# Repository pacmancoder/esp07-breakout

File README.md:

# esp07-breakout
Crude ESP-07 module breakout board intended for toner transfer method DIY PCB production.

Use [Mirrored_Front_Layer.svg](Mirrored_Front_Layer.svg) file for printing with 100% scale;  No additional mirroring required.
Also 2 additional *almost* parallel jumper wires should be placed on the backside of the PCB.

|Render               |Photo              |
|---------------------|-------------------|
|||

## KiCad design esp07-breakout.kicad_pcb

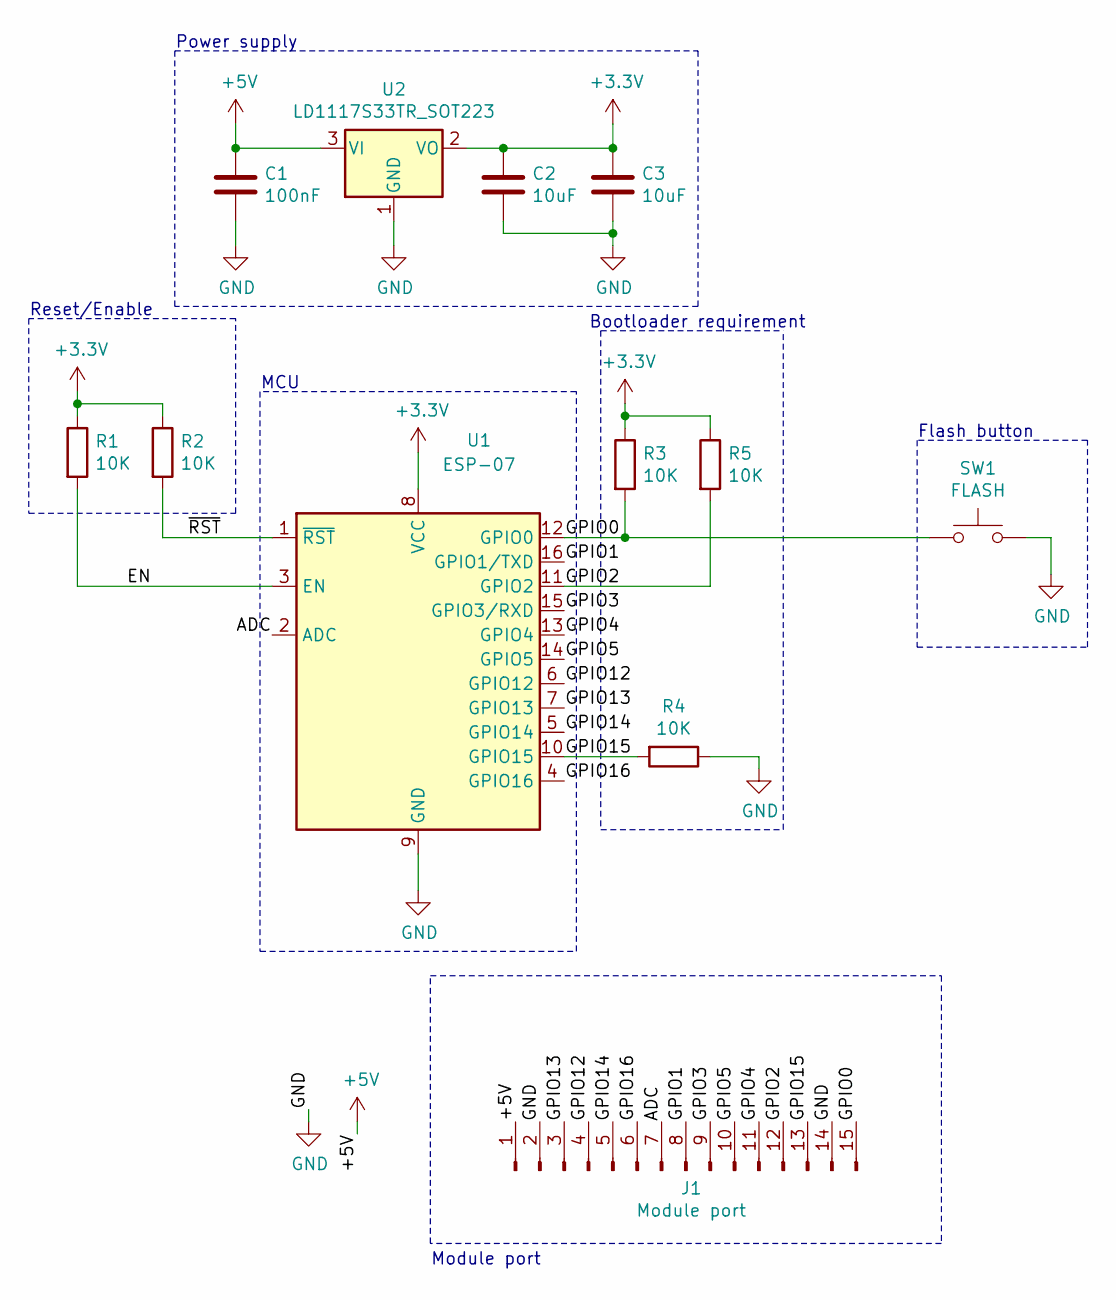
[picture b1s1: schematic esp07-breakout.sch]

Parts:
C1: 100nF; C_0805_2012Metric_Pad1.15x1.40mm_HandSolder
C2, C3: 10uF; C_0805_2012Metric_Pad1.15x1.40mm_HandSolder
J1: Module port; PinHeader_1x15_P2.54mm_Horizontal
R1, R2, R3, R4, R5: 10K; R_0805_2012Metric_Pad1.15x1.40mm_HandSolder
SW1: FLASH; SW_SPST_PTS645
U1: ESP-07
U2: LD1117S33TR_SOT223; SOT-223-3_TabPin2

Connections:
+3V3: C2.1, C3.1, R1.1, R2.1, R3.1, R5.1, U1.8 (VCC), U2.2 (VO)
+5V: C1.1, J1.1, U2.3 (VI)
/ADC: J1.7, U1.2 (ADC)
/EN: R1.2, U1.3 (EN)
/GPIO0: J1.15, R3.2, SW1.1, U1.12 (GPIO0)
/GPIO1: J1.8, U1.16 (GPIO1/TXD)
/GPIO2: J1.12, R5.2, U1.11 (GPIO2)
/GPIO3: J1.9, U1.15 (GPIO3/RXD)
/GPIO4: J1.11, U1.13 (GPIO4)
/GPIO5: J1.10, U1.14 (GPIO5)
/GPIO12: J1.4, U1.6 (GPIO12)
/GPIO13: J1.3, U1.7 (GPIO13)
/GPIO14: J1.5, U1.5 (GPIO14)
/GPIO15: J1.13, R4.2, U1.10 (GPIO15)
/GPIO16: J1.6, U1.4 (GPIO16)
/~RST: R2.2, U1.1 (~RST)
GND: C1.2, C2.2, C3.2, J1.2, J1.14, R4.1, SW1.2, U1.9 (GND), U2.1 (GND)

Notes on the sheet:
Power supply
Reset/Enable
Bootloader requirement
Flash button
Module port
MCU

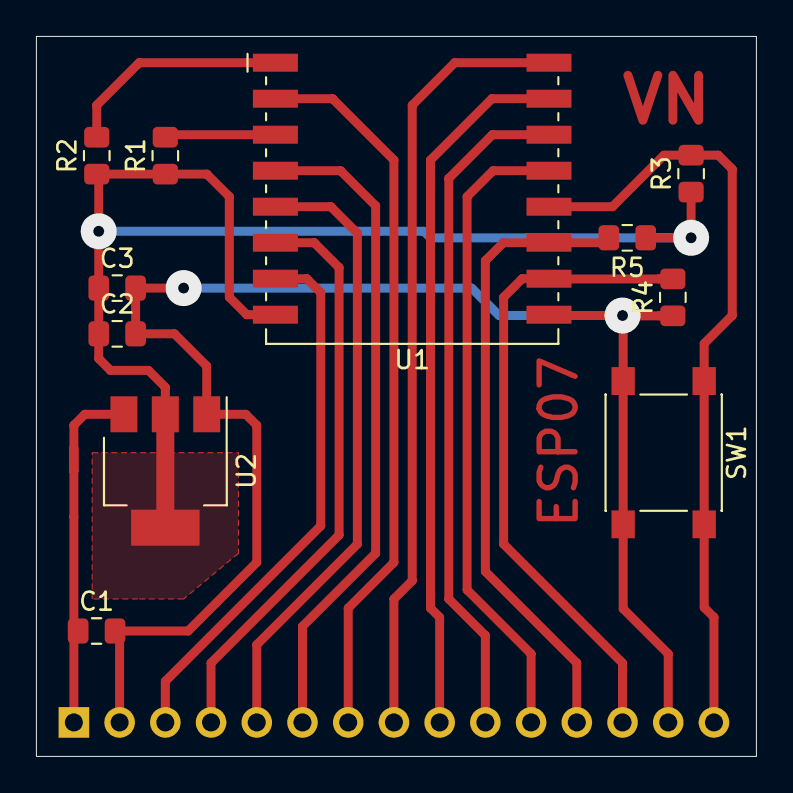
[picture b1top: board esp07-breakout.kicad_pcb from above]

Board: 2 copper layers, 40.0 x 40.0 mm, 12 parts (1 on the bottom side), 17 nets.

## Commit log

2020-09-14 Added LICENSE
2020-09-14 Developed schematics and routed the board; Prepared production file
2020-09-15 Added back layer silkscreen (fixes #1); Added photo
